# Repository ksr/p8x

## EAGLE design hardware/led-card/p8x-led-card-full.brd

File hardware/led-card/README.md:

# LED Output Card (test)

> **Theory of operation:** [p8x-led-card-theory.md](p8x-led-card-theory.md) — deep walkthrough of inputs/outputs, signal flow, and logic.

A minimal memory-mapped **output** card: write a byte to `$FF0C` and its 8 bits
appear on 8 LEDs. Write-only (no readback). It was built primarily as a
**CAD-workflow trial** — a small, self-contained card to exercise the
generate → validate → render → fab pipeline — but it is a complete, standards-
conforming design.

## At a glance

| | |
|---|---|
| Address | `$FF0C` (I/O page, write-only) |
| Function | latch the data byte; drive 8 LEDs from it |
| ICs | 6 (74HCT logic) |

## Chips

| Ref | Device | Role |
|-----|--------|------|
| U1 | 7430 | 8-input NAND — I/O page detect (`A8–A15` all high → `IOPG`) |
| U2 | 74138 | address decode: `A1–A3` select, enabled by `IOPG` + `A4=0`; `Y6` = `$FF0C` |
| U3 | 74138 | `DLD` field decode → `-MEMW` (write strobe) |
| U4 | 74HCT32 | OR gates: `WRSEL` (our-port write) and the latch clock `LCK` |
| U5 | 74HCT14 | inverter — `CLKBN` (the rest of the hex is spare, tied off) |
| U6 | 74374 | the 8-bit LED latch (`!OC` tied low — outputs always enabled) |

Plus the standard support parts: DIN96C edge connector `J1`, per-IC 100 nF
decoupling caps, an 8×330 Ω network `RL1` + 8-LED array `LA1`, a power LED, and a
write-activity LED.

## Use

```
POKE $FF0C, n      ; (monitor: deposit n at FF0C) → n's bit pattern on the LEDs
```

Each bit drives one LED (bit 0 = LED 0 … bit 7 = LED 7); a `1` lights the LED.

## Build

Generated by the canonical generator (run from `hardware/`):

```sh
python3 ../generators/gen_eagle.py                # writes led-card/*.sch + *.brd
python3 ../generators/render_traditional_auto.py  # writes the schematic PDF
```

**Generators are canon** — edit `generators/gen_eagle.py` (the `LED OUTPUT CARD`
section), never the `.sch`/`.brd` directly.

> **Note:** this is a scratch/test card and may be removed. Like the other I/O
> cards it decodes `A1–A4` but not `A5–A7`, so the port aliases every 32 bytes in
> the `$FFxx` page — acceptable for a test, worth tightening if it graduates to a
> permanent card.

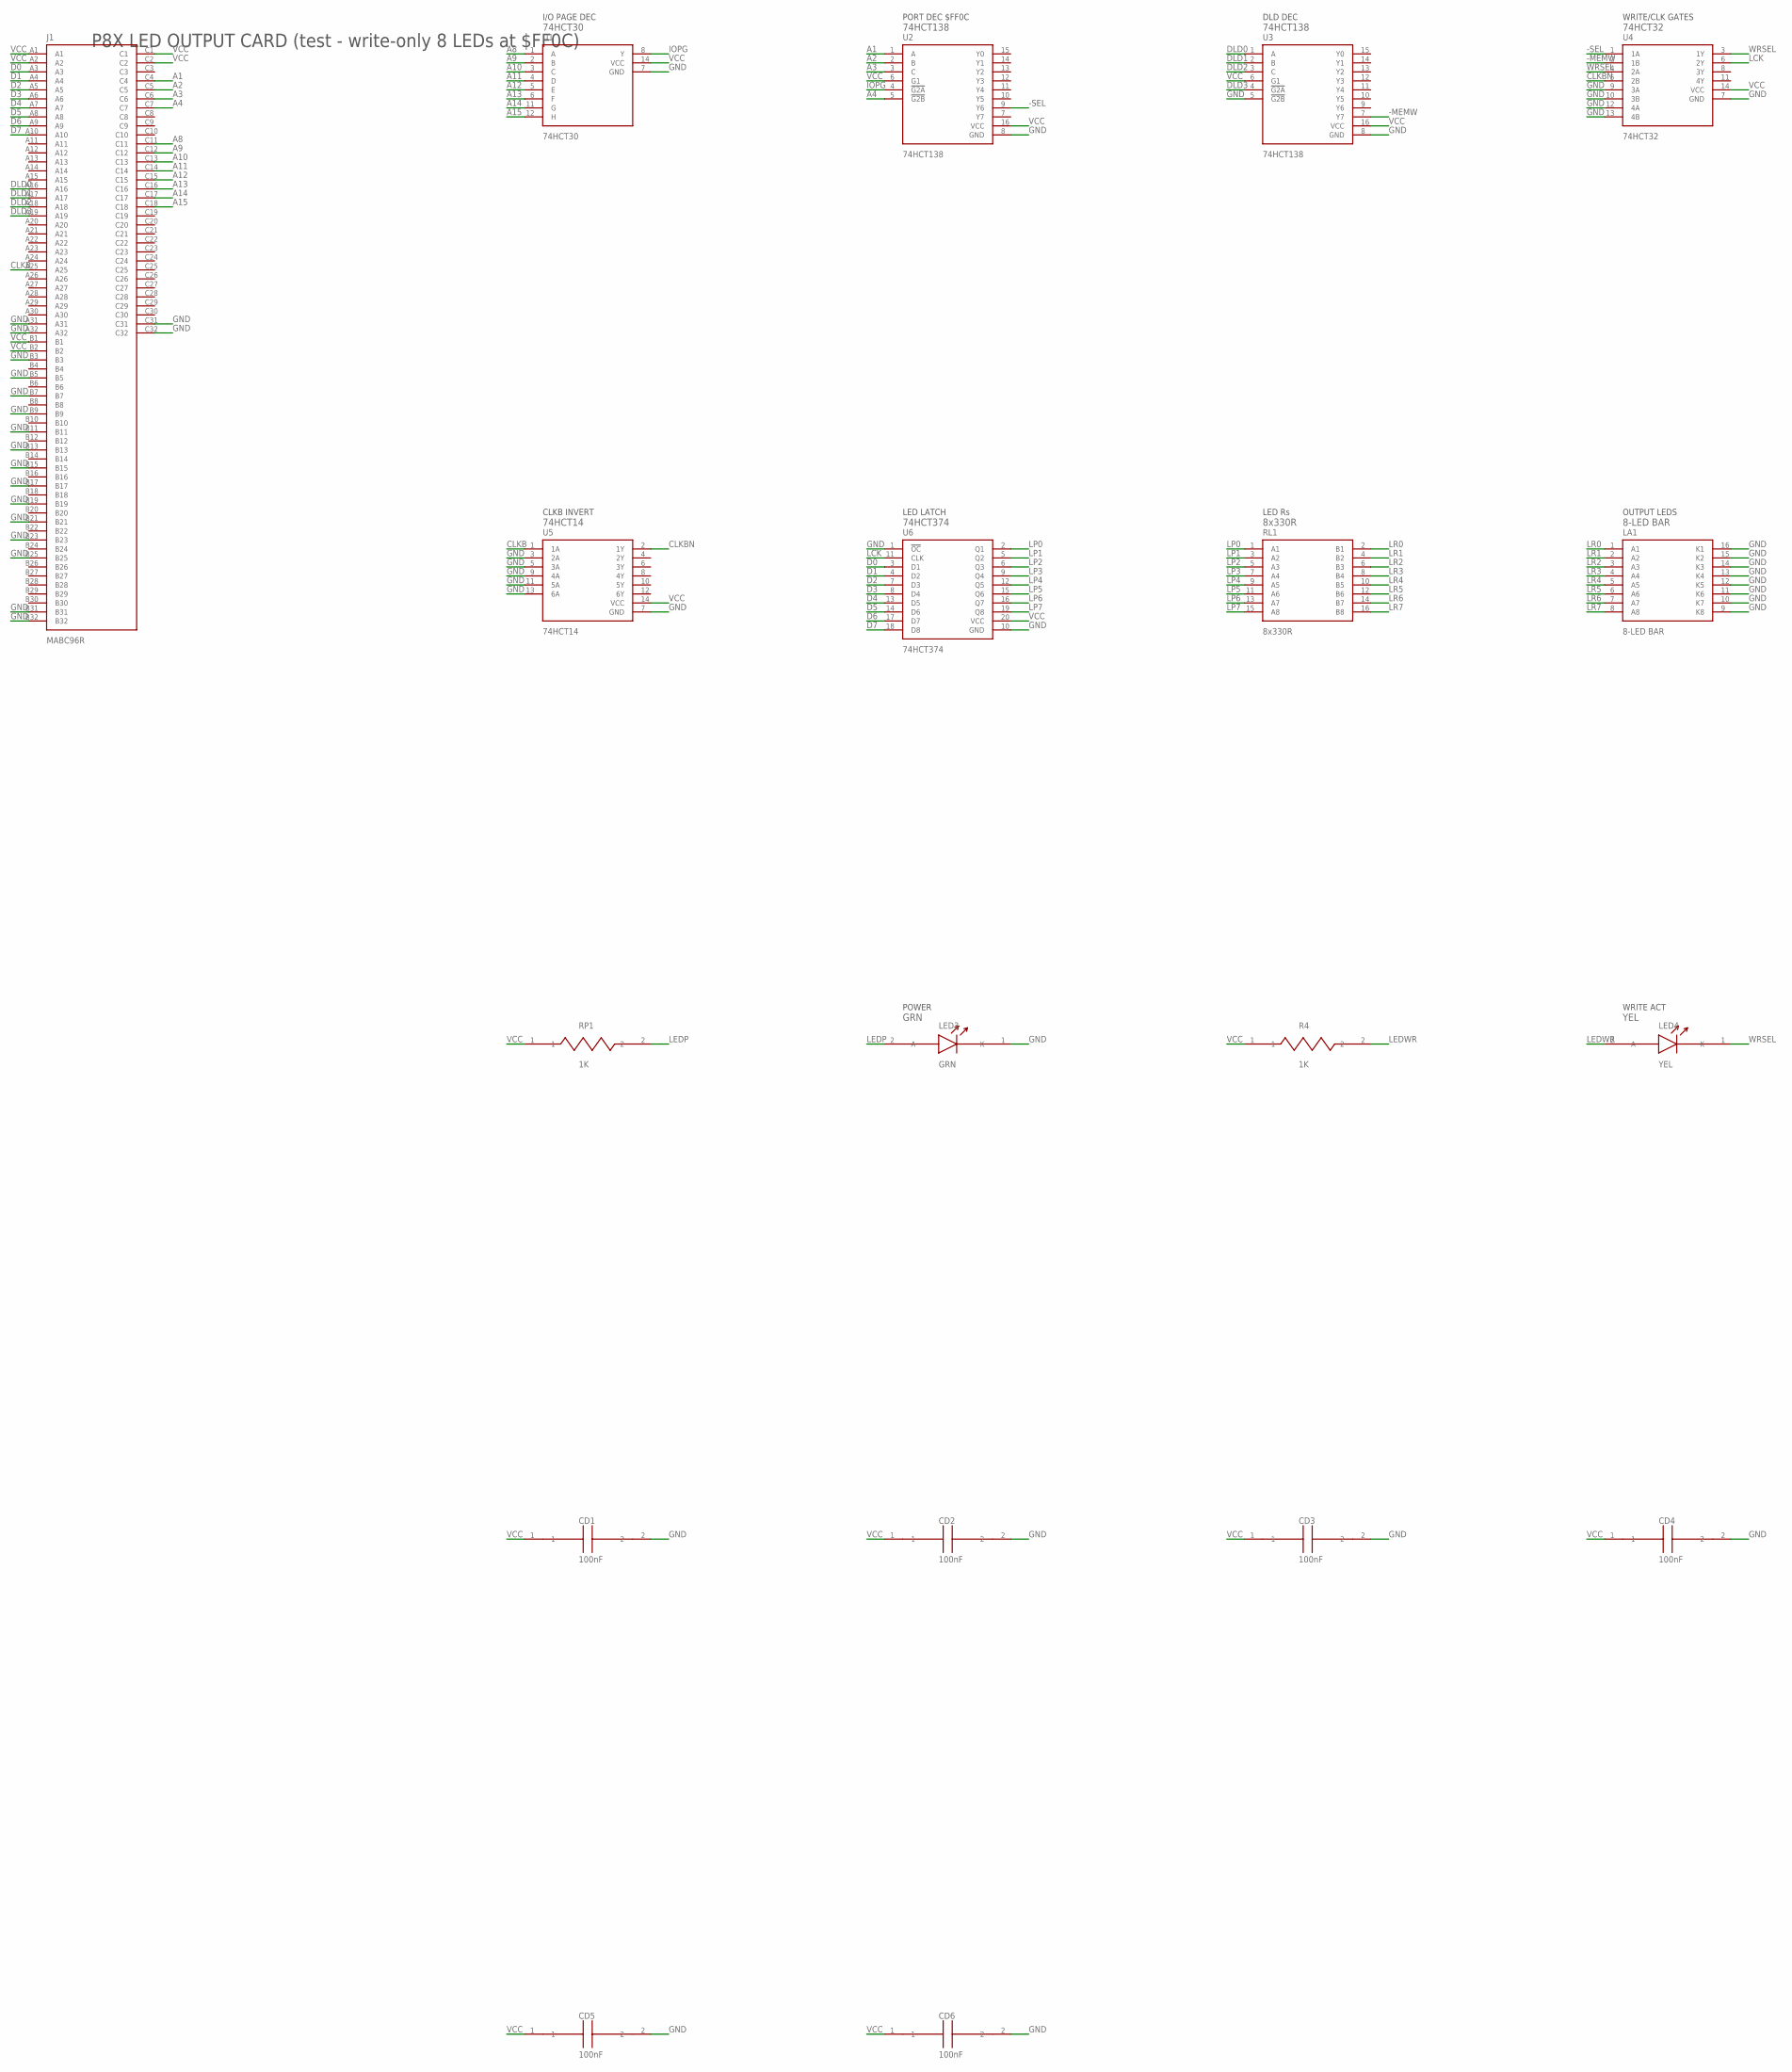
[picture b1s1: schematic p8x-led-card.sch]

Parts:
CD1, CD2, CD3, CD4, CD5, CD6: 100nF; C_DISC1
J1: MABC96R
LA1: 8-LED BAR; DIP16
LED3: GRN; LED5
LED4: YEL; LED5
R4: 1K; R_AXIAL
RL1: 8x330R; SIP16
RP1: 1K; R_AXIAL
U1: 74HCT30; DIP14
U2, U3: 74HCT138; DIP16
U4: 74HCT32; DIP14
U5: 74HCT14; DIP14
U6: 74HCT374; DIP20

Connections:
-MEMW: U3.7 (Y7), U4.2 (1B)
-SEL: U2.9 (Y6), U4.1 (1A)
A1: J1.C4, U2.1 (A)
A2: J1.C5, U2.2 (B)
A3: J1.C6, U2.3 (C)
A4: J1.C7, U2.5 (!G2B)
A8: J1.C11, U1.1 (A)
A9: J1.C12, U1.2 (B)
A10: J1.C13, U1.3 (C)
A11: J1.C14, U1.4 (D)
A12: J1.C15, U1.5 (E)
A13: J1.C16, U1.6 (F)
A14: J1.C17, U1.11 (G)
A15: J1.C18, U1.12 (H)
CLKB: J1.A25, U5.1 (1A)
CLKBN: U4.5 (2B), U5.2 (1Y)
D0: J1.A3, U6.3 (D1)
D1: J1.A4, U6.4 (D2)
D2: J1.A5, U6.7 (D3)
D3: J1.A6, U6.8 (D4)
D4: J1.A7, U6.13 (D5)
D5: J1.A8, U6.14 (D6)
D6: J1.A9, U6.17 (D7)
D7: J1.A10, U6.18 (D8)
DLD0: J1.A16, U3.1 (A)
DLD1: J1.A17, U3.2 (B)
DLD2: J1.A18, U3.3 (C)
DLD3: J1.A19, U3.4 (!G2A)
GND: CD1.2, CD2.2, CD3.2, CD4.2, CD5.2, CD6.2, J1.A31, J1.A32, J1.B3, J1.B5, J1.B7, J1.B9, J1.B11, J1.B13, J1.B15, J1.B17, J1.B19, J1.B21, J1.B23, J1.B25, J1.B31, J1.B32, J1.C31, J1.C32, LA1.9 (K8), LA1.10 (K7), LA1.11 (K6), LA1.12 (K5), LA1.13 (K4), LA1.14 (K3), LA1.15 (K2), LA1.16 (K1), LED3.1 (K), U1.7 (GND), U2.8 (GND), U3.5 (!G2B), U3.8 (GND), U4.7 (GND), U4.9 (3A), U4.10 (3B), U4.12 (4A), U4.13 (4B), U5.3 (2A), U5.5 (3A), U5.7 (GND), U5.9 (4A), U5.11 (5A), U5.13 (6A), U6.1 (!OC), U6.10 (GND)
IOPG: U1.8 (Y), U2.4 (!G2A)
LCK: U4.6 (2Y), U6.11 (CLK)
LEDP: LED3.2 (A), RP1.2
LEDWR: LED4.2 (A), R4.2
LP0: RL1.1 (A1), U6.2 (Q1)
LP1: RL1.3 (A2), U6.5 (Q2)
LP2: RL1.5 (A3), U6.6 (Q3)
LP3: RL1.7 (A4), U6.9 (Q4)
LP4: RL1.9 (A5), U6.12 (Q5)
LP5: RL1.11 (A6), U6.15 (Q6)
LP6: RL1.13 (A7), U6.16 (Q7)
LP7: RL1.15 (A8), U6.19 (Q8)
LR0: LA1.1 (A1), RL1.2 (B1)
LR1: LA1.2 (A2), RL1.4 (B2)
LR2: LA1.3 (A3), RL1.6 (B3)
LR3: LA1.4 (A4), RL1.8 (B4)
LR4: LA1.5 (A5), RL1.10 (B5)
LR5: LA1.6 (A6), RL1.12 (B6)
LR6: LA1.7 (A7), RL1.14 (B7)
LR7: LA1.8 (A8), RL1.16 (B8)
VCC: CD1.1, CD2.1, CD3.1, CD4.1, CD5.1, CD6.1, J1.A1, J1.A2, J1.B1, J1.B2, J1.C1, J1.C2, R4.1, RP1.1, U1.14 (VCC), U2.6 (G1), U2.16 (VCC), U3.6 (G1), U3.16 (VCC), U4.14 (VCC), U5.14 (VCC), U6.20 (VCC)
WRSEL: LED4.1 (K), U4.3 (1Y), U4.4 (2A)

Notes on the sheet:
P8X LED OUTPUT CARD (test - write-only 8 LEDs at $FF0C)
I/O PAGE DEC
74HCT30
PORT DEC $FF0C
74HCT138
DLD DEC
WRITE/CLK GATES
74HCT32
CLKB INVERT
74HCT14
LED LATCH
74HCT374
LED Rs
8x330R
OUTPUT LEDS
8-LED BAR
POWER
GRN
WRITE ACT
YEL

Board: 4 copper layers, 19 parts (0 on the bottom side), 51 nets, no tracks yet.

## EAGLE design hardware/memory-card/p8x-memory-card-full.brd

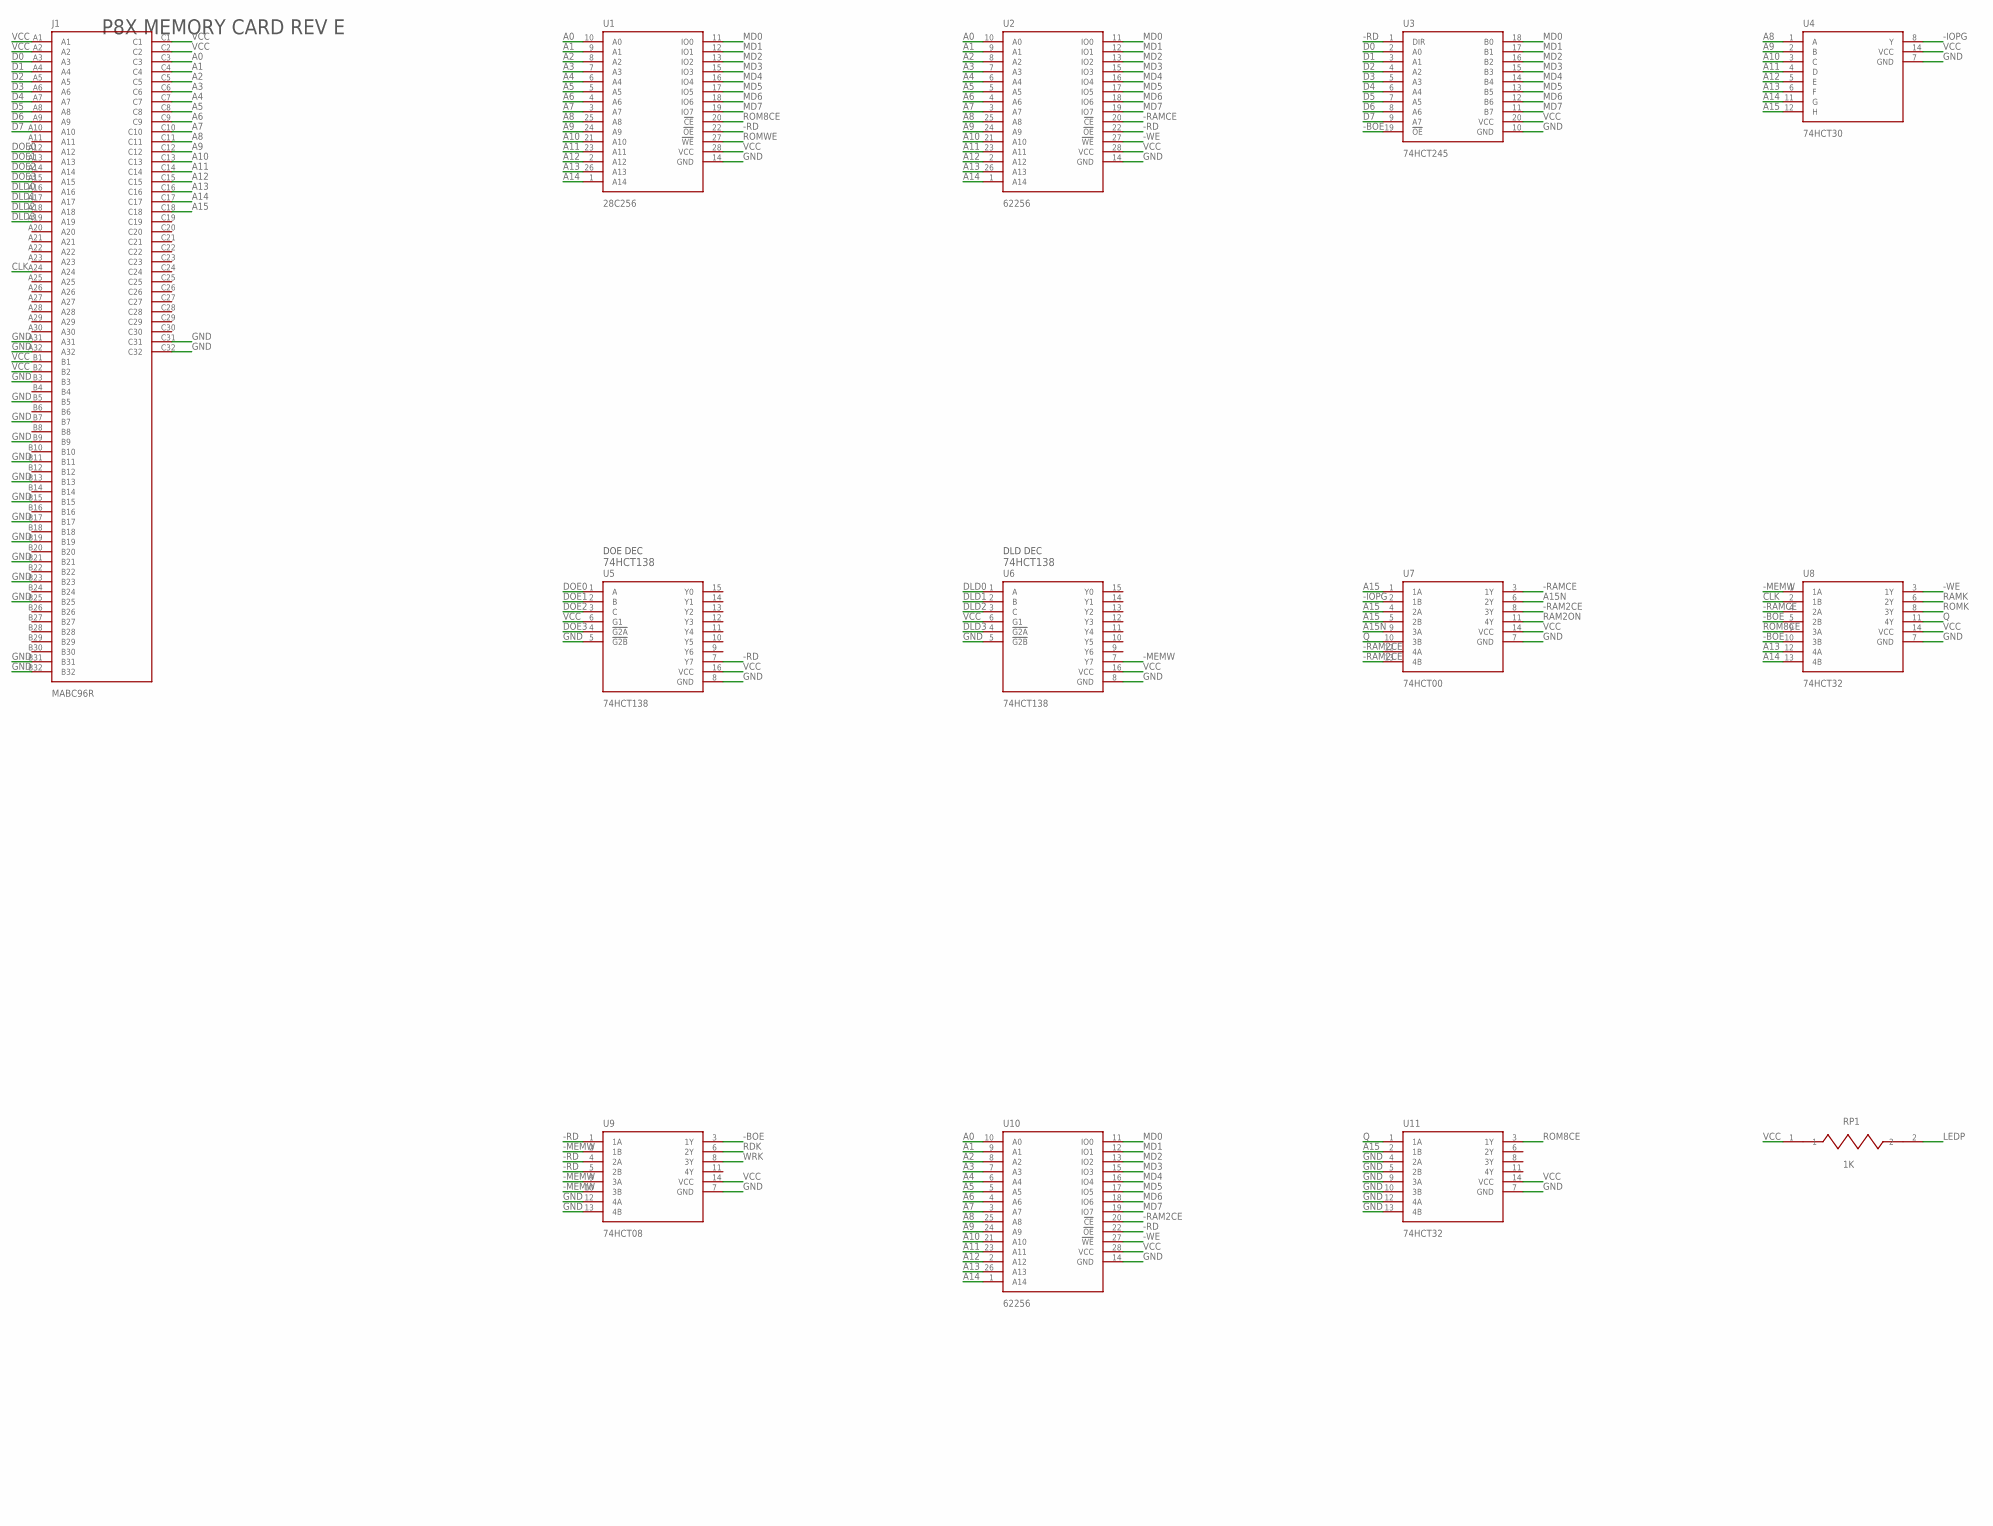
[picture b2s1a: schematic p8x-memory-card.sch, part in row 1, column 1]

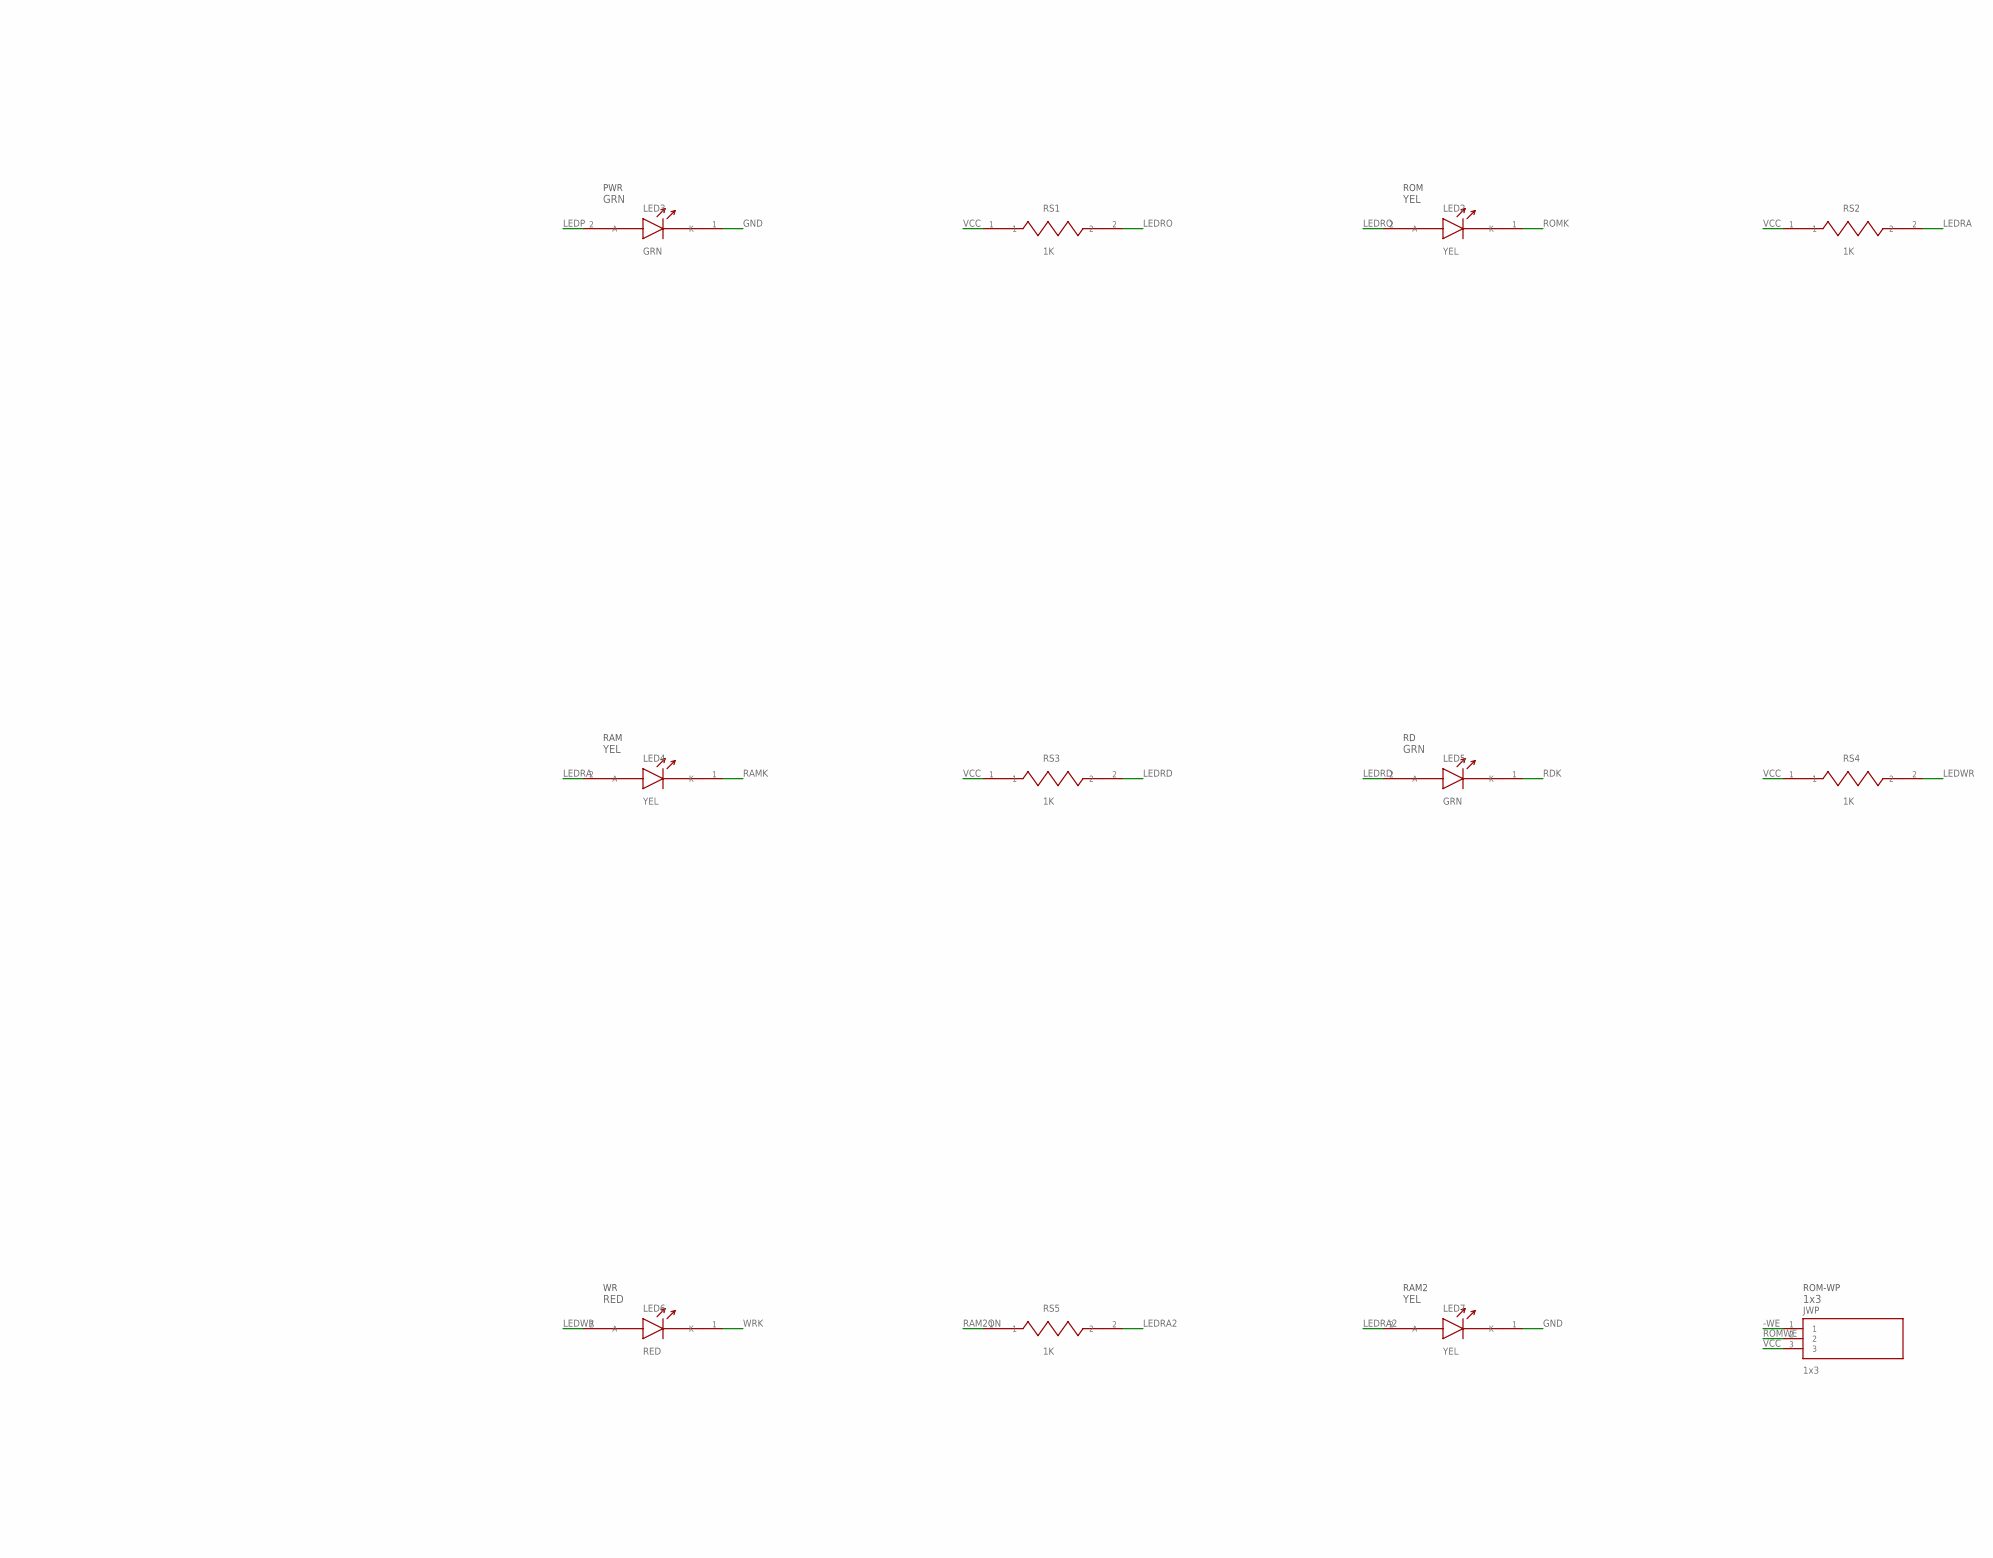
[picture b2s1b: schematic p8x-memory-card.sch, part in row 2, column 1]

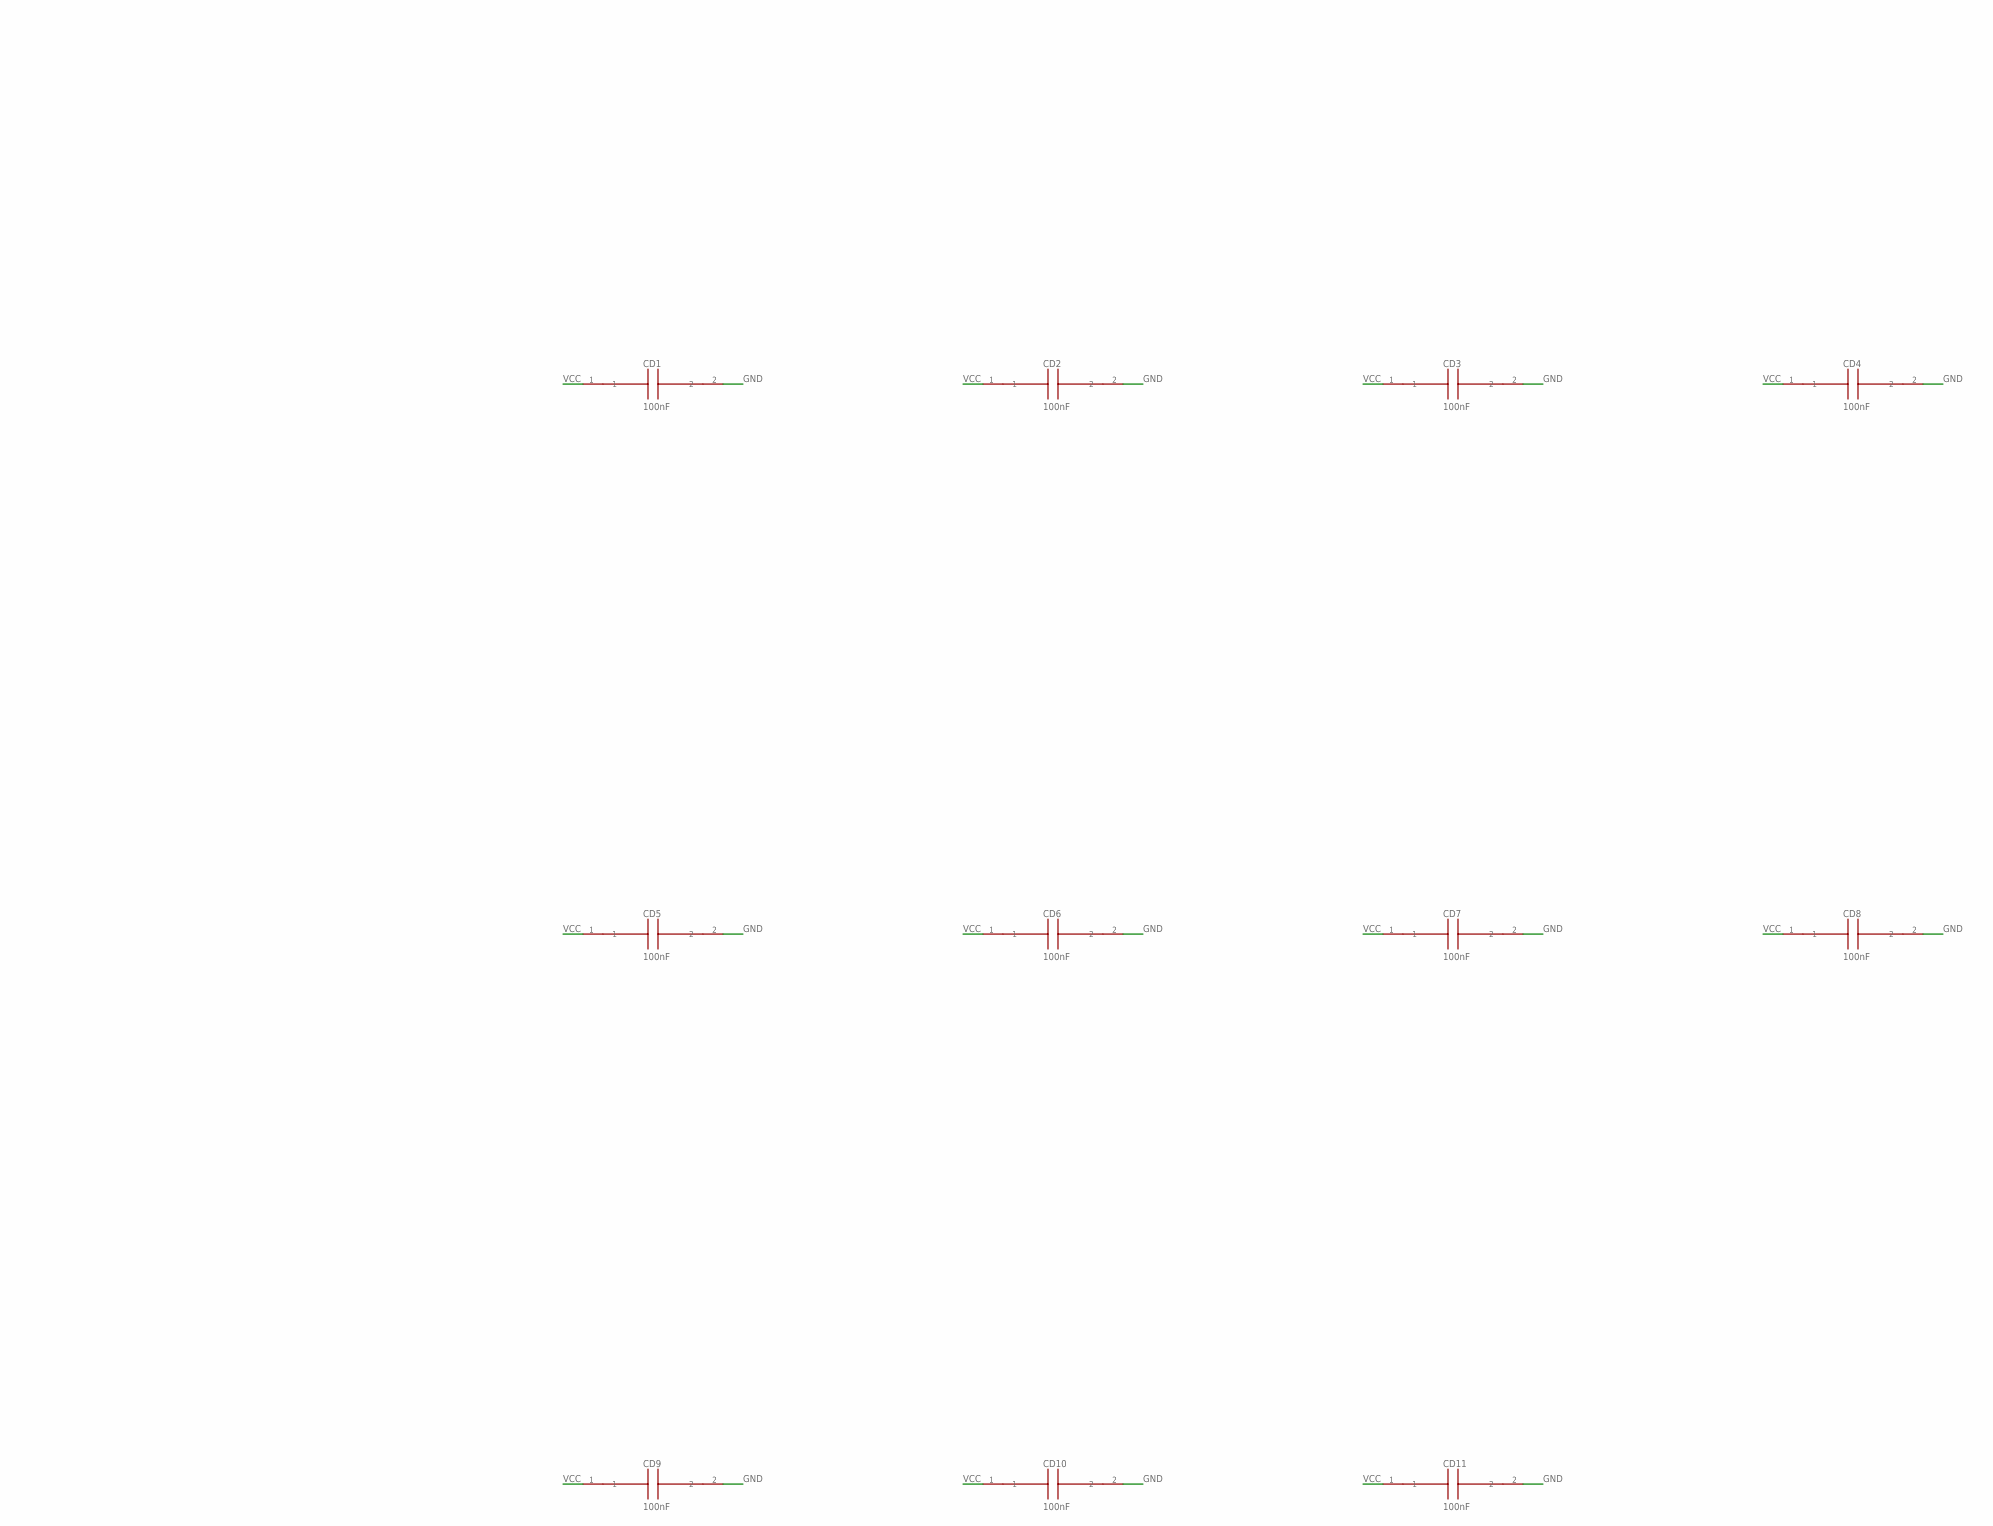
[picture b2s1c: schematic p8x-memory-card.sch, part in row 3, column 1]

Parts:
CD1, CD2, CD3, CD4, CD5, CD6, CD7, CD8, CD9, CD10, CD11: 100nF; C_DISC1
J1: MABC96R
JWP: 1x3; HDR3
LED2, LED4, LED7: YEL; LED5
LED3, LED5: GRN; LED5
LED6: RED; LED5
RP1: 1K; R_AXIAL
RS1, RS2, RS3, RS4, RS5: 1K; R_AXIAL
U1: 28C256; DIP28W
U2, U10: 62256; DIP28W
U3: 74HCT245; DIP20
U4: 74HCT30; DIP14
U5, U6: 74HCT138; DIP16
U7: 74HCT00; DIP14
U8, U11: 74HCT32; DIP14
U9: 74HCT08; DIP14

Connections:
-BOE: U3.19 (!OE), U8.5 (2B), U8.10 (3B), U9.3 (1Y)
-IOPG: U4.8 (Y), U7.2 (1B)
-MEMW: U6.7 (Y7), U8.1 (1A), U9.2 (1B), U9.9 (3A), U9.10 (3B)
-RAM2CE: U7.8 (3Y), U7.12 (4A), U7.13 (4B), U10.20 (!CE)
-RAMCE: U2.20 (!CE), U7.3 (1Y), U8.4 (2A)
-RD: U1.22 (!OE), U2.22 (!OE), U3.1 (DIR), U5.7 (Y7), U9.1 (1A), U9.4 (2A), U9.5 (2B), U10.22 (!OE)
-WE: JWP.1, U2.27 (!WE), U8.3 (1Y), U10.27 (!WE)
A0: J1.C3, U1.10 (A0), U2.10 (A0), U10.10 (A0)
A1: J1.C4, U1.9 (A1), U2.9 (A1), U10.9 (A1)
A2: J1.C5, U1.8 (A2), U2.8 (A2), U10.8 (A2)
A3: J1.C6, U1.7 (A3), U2.7 (A3), U10.7 (A3)
A4: J1.C7, U1.6 (A4), U2.6 (A4), U10.6 (A4)
A5: J1.C8, U1.5 (A5), U2.5 (A5), U10.5 (A5)
A6: J1.C9, U1.4 (A6), U2.4 (A6), U10.4 (A6)
A7: J1.C10, U1.3 (A7), U2.3 (A7), U10.3 (A7)
A8: J1.C11, U1.25 (A8), U2.25 (A8), U4.1 (A), U10.25 (A8)
A9: J1.C12, U1.24 (A9), U2.24 (A9), U4.2 (B), U10.24 (A9)
A10: J1.C13, U1.21 (A10), U2.21 (A10), U4.3 (C), U10.21 (A10)
A11: J1.C14, U1.23 (A11), U2.23 (A11), U4.4 (D), U10.23 (A11)
A12: J1.C15, U1.2 (A12), U2.2 (A12), U4.5 (E), U10.2 (A12)
A13: J1.C16, U1.26 (A13), U2.26 (A13), U4.6 (F), U8.12 (4A), U10.26 (A13)
A14: J1.C17, U1.1 (A14), U2.1 (A14), U4.11 (G), U8.13 (4B), U10.1 (A14)
A15: J1.C18, U4.12 (H), U7.1 (1A), U7.4 (2A), U7.5 (2B), U11.2 (1B)
A15N: U7.6 (2Y), U7.9 (3A)
CLK: J1.A24, U8.2 (1B)
D0: J1.A3, U3.2 (A0)
D1: J1.A4, U3.3 (A1)
D2: J1.A5, U3.4 (A2)
D3: J1.A6, U3.5 (A3)
D4: J1.A7, U3.6 (A4)
D5: J1.A8, U3.7 (A5)
D6: J1.A9, U3.8 (A6)
D7: J1.A10, U3.9 (A7)
DLD0: J1.A16, U6.1 (A)
DLD1: J1.A17, U6.2 (B)
DLD2: J1.A18, U6.3 (C)
DLD3: J1.A19, U6.4 (!G2A)
DOE0: J1.A12, U5.1 (A)
DOE1: J1.A13, U5.2 (B)
DOE2: J1.A14, U5.3 (C)
DOE3: J1.A15, U5.4 (!G2A)
GND: CD1.2, CD2.2, CD3.2, CD4.2, CD5.2, CD6.2, CD7.2, CD8.2, CD9.2, CD10.2, CD11.2, J1.A31, J1.A32, J1.B3, J1.B5, J1.B7, J1.B9, J1.B11, J1.B13, J1.B15, J1.B17, J1.B19, J1.B21, J1.B23, J1.B25, J1.B31, J1.B32, J1.C31, J1.C32, LED3.1 (K), LED7.1 (K), U1.14 (GND), U2.14 (GND), U3.10 (GND), U4.7 (GND), U5.5 (!G2B), U5.8 (GND), U6.5 (!G2B), U6.8 (GND), U7.7 (GND), U8.7 (GND), U9.7 (GND), U9.12 (4A), U9.13 (4B), U10.14 (GND), U11.4 (2A), U11.5 (2B), U11.7 (GND), U11.9 (3A), U11.10 (3B), U11.12 (4A), U11.13 (4B)
LEDP: LED3.2 (A), RP1.2
LEDRA: LED4.2 (A), RS2.2
LEDRA2: LED7.2 (A), RS5.2
LEDRD: LED5.2 (A), RS3.2
LEDRO: LED2.2 (A), RS1.2
LEDWR: LED6.2 (A), RS4.2
MD0: U1.11 (IO0), U2.11 (IO0), U3.18 (B0), U10.11 (IO0)
MD1: U1.12 (IO1), U2.12 (IO1), U3.17 (B1), U10.12 (IO1)
MD2: U1.13 (IO2), U2.13 (IO2), U3.16 (B2), U10.13 (IO2)
MD3: U1.15 (IO3), U2.15 (IO3), U3.15 (B3), U10.15 (IO3)
MD4: U1.16 (IO4), U2.16 (IO4), U3.14 (B4), U10.16 (IO4)
MD5: U1.17 (IO5), U2.17 (IO5), U3.13 (B5), U10.17 (IO5)
MD6: U1.18 (IO6), U2.18 (IO6), U3.12 (B6), U10.18 (IO6)
MD7: U1.19 (IO7), U2.19 (IO7), U3.11 (B7), U10.19 (IO7)
Q: U7.10 (3B), U8.11 (4Y), U11.1 (1A)
RAM2ON: RS5.1, U7.11 (4Y)
RAMK: LED4.1 (K), U8.6 (2Y)
RDK: LED5.1 (K), U9.6 (2Y)
ROM8CE: U1.20 (!CE), U8.9 (3A), U11.3 (1Y)
ROMK: LED2.1 (K), U8.8 (3Y)
ROMWE: JWP.2, U1.27 (!WE)
VCC: CD1.1, CD2.1, CD3.1, CD4.1, CD5.1, CD6.1, CD7.1, CD8.1, CD9.1, CD10.1, CD11.1, J1.A1, J1.A2, J1.B1, J1.B2, J1.C1, J1.C2, JWP.3, RP1.1, RS1.1, RS2.1, RS3.1, RS4.1, U1.28 (VCC), U2.28 (VCC), U3.20 (VCC), U4.14 (VCC), U5.6 (G1), U5.16 (VCC), U6.6 (G1), U6.16 (VCC), U7.14 (VCC), U8.14 (VCC), U9.14 (VCC), U10.28 (VCC), U11.14 (VCC)
WRK: LED6.1 (K), U9.8 (3Y)

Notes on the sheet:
P8X MEMORY CARD REV E
DOE DEC
74HCT138
DLD DEC
PWR
GRN
ROM
YEL
RAM
RED
RAM2
ROM-WP
1x3

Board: 4 copper layers, 36 parts (0 on the bottom side), 65 nets, no tracks yet.
